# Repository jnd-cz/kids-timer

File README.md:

# Kids timer

Rev 1 PCB design and a MicroPython countdown timer for the RP2354A. The firmware
supports a seven-segment countdown, minute and second LED rings, ambient-light
brightness, audio and songs, battery and sensor readouts, a level, and a touch
pad test.

- [Firmware installation, features and controls](firmware/README.md)
- [Board bring-up and GPIO map](BRINGUP.md)
- [Display power estimate and measurement plan](firmware/POWER.md)
- [Production files for Rev 1](production/)

The firmware is an evolving hardware prototype. See the firmware guide for
features that still need board verification and the 2 MB flash check before
copying files to the device. Run host-side logic checks with
`python -m unittest discover -s tests -v`.

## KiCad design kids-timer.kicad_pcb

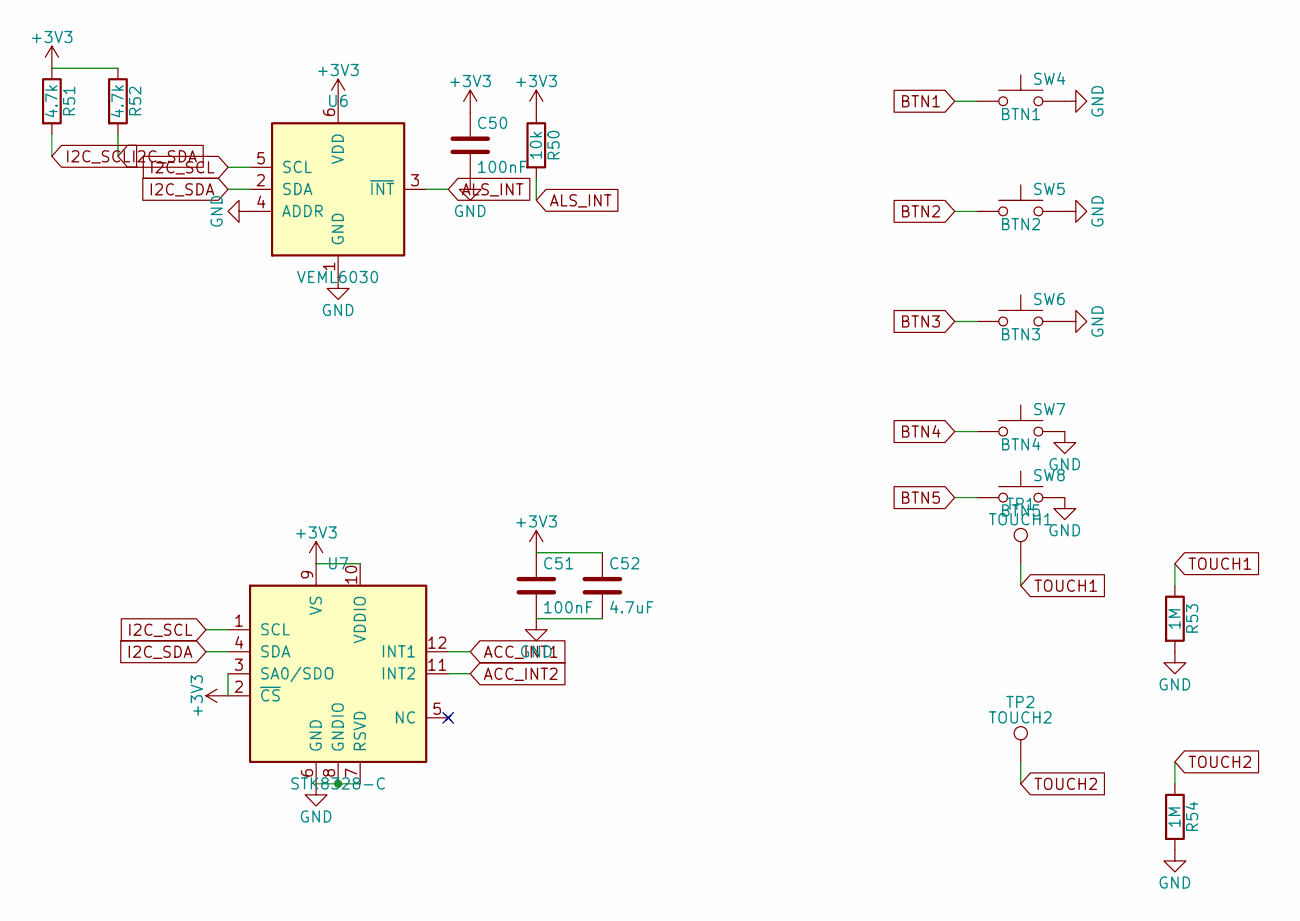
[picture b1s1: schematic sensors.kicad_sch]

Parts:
C50, C51: 100nF; C_0402_1005Metric; LCSC C1525
C52: 4.7uF; C_0402_1005Metric; LCSC C23733
R50: 10k; R_0402_1005Metric; LCSC C25744
R51, R52: 4.7k; R_0402_1005Metric; LCSC C25900
R53, R54: 1M; R_0402_1005Metric; LCSC C26083
SW4: BTN1; SW_SPST_XUNPU_TS-1088_3.9x3mm; MPN TS-1088-AR02016; LCSC C720477
SW5: BTN2; SW_SPST_XUNPU_TS-1088_3.9x3mm; MPN TS-1088-AR02016; LCSC C720477
SW6: BTN3; SW_SPST_XUNPU_TS-1088_3.9x3mm; MPN TS-1088-AR02016; LCSC C720477
SW7: BTN4; SW_SPST_XUNPU_TS-1088_3.9x3mm; MPN TS-1088-AR02016; LCSC C720477
SW8: BTN5; SW_SPST_XUNPU_TS-1088_3.9x3mm; MPN TS-1088-AR02016; LCSC C720477
TP1: TOUCH1; TouchPad_D12mm
TP2: TOUCH2; TouchPad_D12mm
U6: VEML6030; Vishay_VEML6030_2x2mm; MPN VEML6030; LCSC C132182
U7: STK8328-C; LGA-12_2x2mm_P0.5mm; MPN STK8328-C; LCSC C49230199

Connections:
+3V3: C50.1, C51.1, C52.1, R50.1, R51.1, R52.1, U6.6 (VDD), U7.2 (~CS), U7.3 (SA0/SDO), U7.9 (VS), U7.10 (VDDIO); also elsewhere on the board
ACC_INT1: U7.12 (INT1); also elsewhere on the board
ACC_INT2: U7.11 (INT2); also elsewhere on the board
ALS_INT: R50.2, U6.3 (~INT); also elsewhere on the board
BTN1: SW4.1; also elsewhere on the board
BTN2: SW5.1; also elsewhere on the board
BTN3: SW6.1; also elsewhere on the board
BTN4: SW7.1; also elsewhere on the board
BTN5: SW8.1; also elsewhere on the board
I2C_SCL: R51.2, U6.5 (SCL), U7.1 (SCL); also elsewhere on the board
I2C_SDA: R52.2, U6.2 (SDA), U7.4 (SDA); also elsewhere on the board
TOUCH1: R53.1, TP1.1 (1_1); also elsewhere on the board
TOUCH2: R54.1, TP2.1 (1_1); also elsewhere on the board

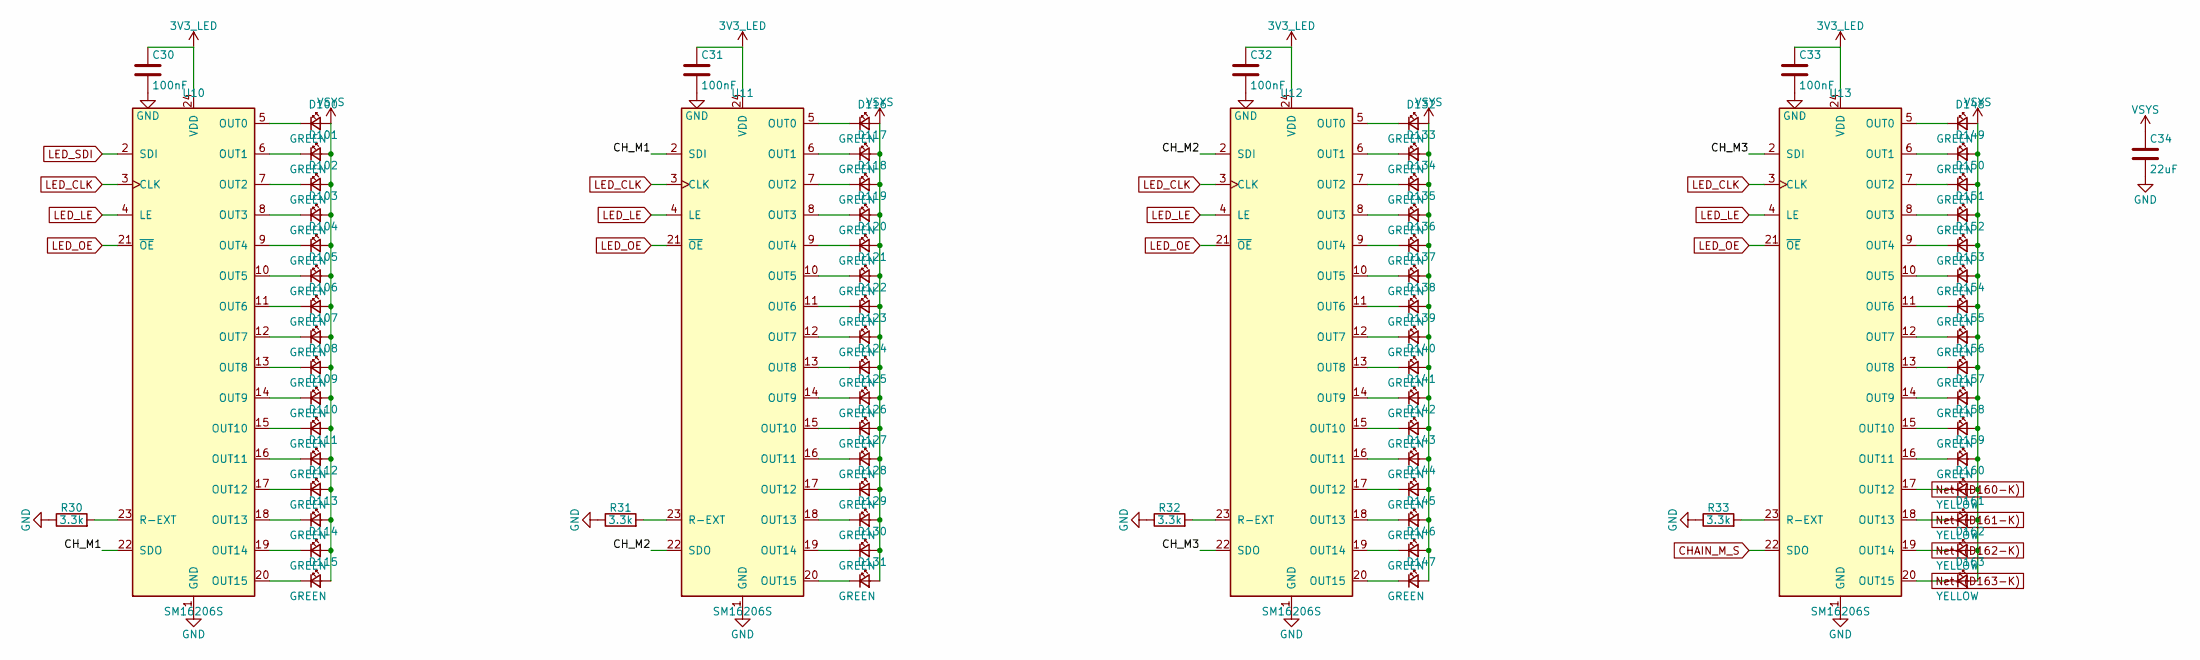
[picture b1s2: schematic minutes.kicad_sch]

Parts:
C30, C31, C32, C33: 100nF; C_0402_1005Metric; LCSC C1525
C34: 22uF; C_0805_2012Metric; LCSC C45783
D100, D101, D102, D103, D104, D105, D106, D107, D108, D109, D110, D111, D112, D113, D114, D115, D116, D117, D118, D119, D120, D121, D122, D123, D124, D125, D126, D127, D128, D129, D130, D131, D132, D133, D134, D135, D136, D137, D138, D139, D140, D141, D142, D143, D144, D145, D146, D147, D148, D149, D150, D151, D152, D153, D154, D155, D156, D157, D158, D159: GREEN; LED_0805_2012Metric_Ring; MPN KT-0805G; LCSC C2297
D160, D161, D162, D163: YELLOW; LED_0805_2012Metric; MPN KT-0805Y; LCSC C2296
R30, R31, R32, R33: 3.3k; R_0402_1005Metric; LCSC C25890
U10, U11, U12, U13: SM16206S; QSOP-24_3.9x8.7mm_P0.635mm; MPN SM16206S; LCSC C121618

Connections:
3V3_LED: C30.1, C31.1, C32.1, C33.1, U10.24 (VDD), U11.24 (VDD), U12.24 (VDD), U13.24 (VDD); also elsewhere on the board
/Minutes ring/CH_M1: U10.22 (SDO), U11.2 (SDI)
/Minutes ring/CH_M2: U11.22 (SDO), U12.2 (SDI)
/Minutes ring/CH_M3: U12.22 (SDO), U13.2 (SDI)
CHAIN_M_S: U13.22 (SDO); also elsewhere on the board
LED_CLK: U10.3 (CLK), U11.3 (CLK), U12.3 (CLK), U13.3 (CLK); also elsewhere on the board
LED_LE: U10.4 (LE), U11.4 (LE), U12.4 (LE), U13.4 (LE); also elsewhere on the board
LED_OE: U10.21 (~OE), U11.21 (~OE), U12.21 (~OE), U13.21 (~OE); also elsewhere on the board
LED_SDI: U10.2 (SDI); also elsewhere on the board
unnamed: D100.1 (K), U10.5 (OUT0)
unnamed: D101.1 (K), U10.6 (OUT1)
unnamed: D102.1 (K), U10.7 (OUT2)
unnamed: D103.1 (K), U10.8 (OUT3)
unnamed: D104.1 (K), U10.9 (OUT4)
unnamed: D105.1 (K), U10.10 (OUT5)
unnamed: D106.1 (K), U10.11 (OUT6)
unnamed: D107.1 (K), U10.12 (OUT7)
unnamed: D108.1 (K), U10.13 (OUT8)
unnamed: D109.1 (K), U10.14 (OUT9)
unnamed: D110.1 (K), U10.15 (OUT10)
unnamed: D111.1 (K), U10.16 (OUT11)
unnamed: D112.1 (K), U10.17 (OUT12)
unnamed: D113.1 (K), U10.18 (OUT13)
unnamed: D114.1 (K), U10.19 (OUT14)
unnamed: D115.1 (K), U10.20 (OUT15)
unnamed: D116.1 (K), U11.5 (OUT0)
unnamed: D117.1 (K), U11.6 (OUT1)
unnamed: D118.1 (K), U11.7 (OUT2)
unnamed: D119.1 (K), U11.8 (OUT3)
unnamed: D120.1 (K), U11.9 (OUT4)
unnamed: D121.1 (K), U11.10 (OUT5)
unnamed: D122.1 (K), U11.11 (OUT6)
unnamed: D123.1 (K), U11.12 (OUT7)
unnamed: D124.1 (K), U11.13 (OUT8)
unnamed: D125.1 (K), U11.14 (OUT9)
unnamed: D126.1 (K), U11.15 (OUT10)
unnamed: D127.1 (K), U11.16 (OUT11)
unnamed: D128.1 (K), U11.17 (OUT12)
unnamed: D129.1 (K), U11.18 (OUT13)
unnamed: D130.1 (K), U11.19 (OUT14)
unnamed: D131.1 (K), U11.20 (OUT15)
unnamed: D132.1 (K), U12.5 (OUT0)
unnamed: D133.1 (K), U12.6 (OUT1)
unnamed: D134.1 (K), U12.7 (OUT2)
unnamed: D135.1 (K), U12.8 (OUT3)
unnamed: D136.1 (K), U12.9 (OUT4)
unnamed: D137.1 (K), U12.10 (OUT5)
unnamed: D138.1 (K), U12.11 (OUT6)
unnamed: D139.1 (K), U12.12 (OUT7)
unnamed: D140.1 (K), U12.13 (OUT8)
unnamed: D141.1 (K), U12.14 (OUT9)
unnamed: D142.1 (K), U12.15 (OUT10)
unnamed: D143.1 (K), U12.16 (OUT11)
unnamed: D144.1 (K), U12.17 (OUT12)
unnamed: D145.1 (K), U12.18 (OUT13)
unnamed: D146.1 (K), U12.19 (OUT14)
unnamed: D147.1 (K), U12.20 (OUT15)
unnamed: D148.1 (K), U13.5 (OUT0)
unnamed: D149.1 (K), U13.6 (OUT1)
unnamed: D150.1 (K), U13.7 (OUT2)
unnamed: D151.1 (K), U13.8 (OUT3)
unnamed: D152.1 (K), U13.9 (OUT4)
unnamed: D153.1 (K), U13.10 (OUT5)
unnamed: D154.1 (K), U13.11 (OUT6)
unnamed: D155.1 (K), U13.12 (OUT7)
unnamed: D156.1 (K), U13.13 (OUT8)
unnamed: D157.1 (K), U13.14 (OUT9)
unnamed: D158.1 (K), U13.15 (OUT10)
unnamed: D159.1 (K), U13.16 (OUT11)
unnamed: D160.1 (K), U13.17 (OUT12)
unnamed: D161.1 (K), U13.18 (OUT13)
unnamed: D162.1 (K), U13.19 (OUT14)
unnamed: D163.1 (K), U13.20 (OUT15)
unnamed: R30.2, U10.23 (R-EXT)
unnamed: R31.2, U11.23 (R-EXT)
unnamed: R32.2, U12.23 (R-EXT)
unnamed: R33.2, U13.23 (R-EXT)
VSYS: C34.1, D100.2 (A), D101.2 (A), D102.2 (A), D103.2 (A), D104.2 (A), D105.2 (A), D106.2 (A), D107.2 (A), D108.2 (A), D109.2 (A), D110.2 (A), D111.2 (A), D112.2 (A), D113.2 (A), D114.2 (A), D115.2 (A), D116.2 (A), D117.2 (A), D118.2 (A), D119.2 (A), D120.2 (A), D121.2 (A), D122.2 (A), D123.2 (A), D124.2 (A), D125.2 (A), D126.2 (A), D127.2 (A), D128.2 (A), D129.2 (A), D130.2 (A), D131.2 (A), D132.2 (A), D133.2 (A), D134.2 (A), D135.2 (A), D136.2 (A), D137.2 (A), D138.2 (A), D139.2 (A), D140.2 (A), D141.2 (A), D142.2 (A), D143.2 (A), D144.2 (A), D145.2 (A), D146.2 (A), D147.2 (A), D148.2 (A), D149.2 (A), D150.2 (A), D151.2 (A), D152.2 (A), D153.2 (A), D154.2 (A), D155.2 (A), D156.2 (A), D157.2 (A), D158.2 (A), D159.2 (A), D160.2 (A), D161.2 (A), D162.2 (A), D163.2 (A); also elsewhere on the board

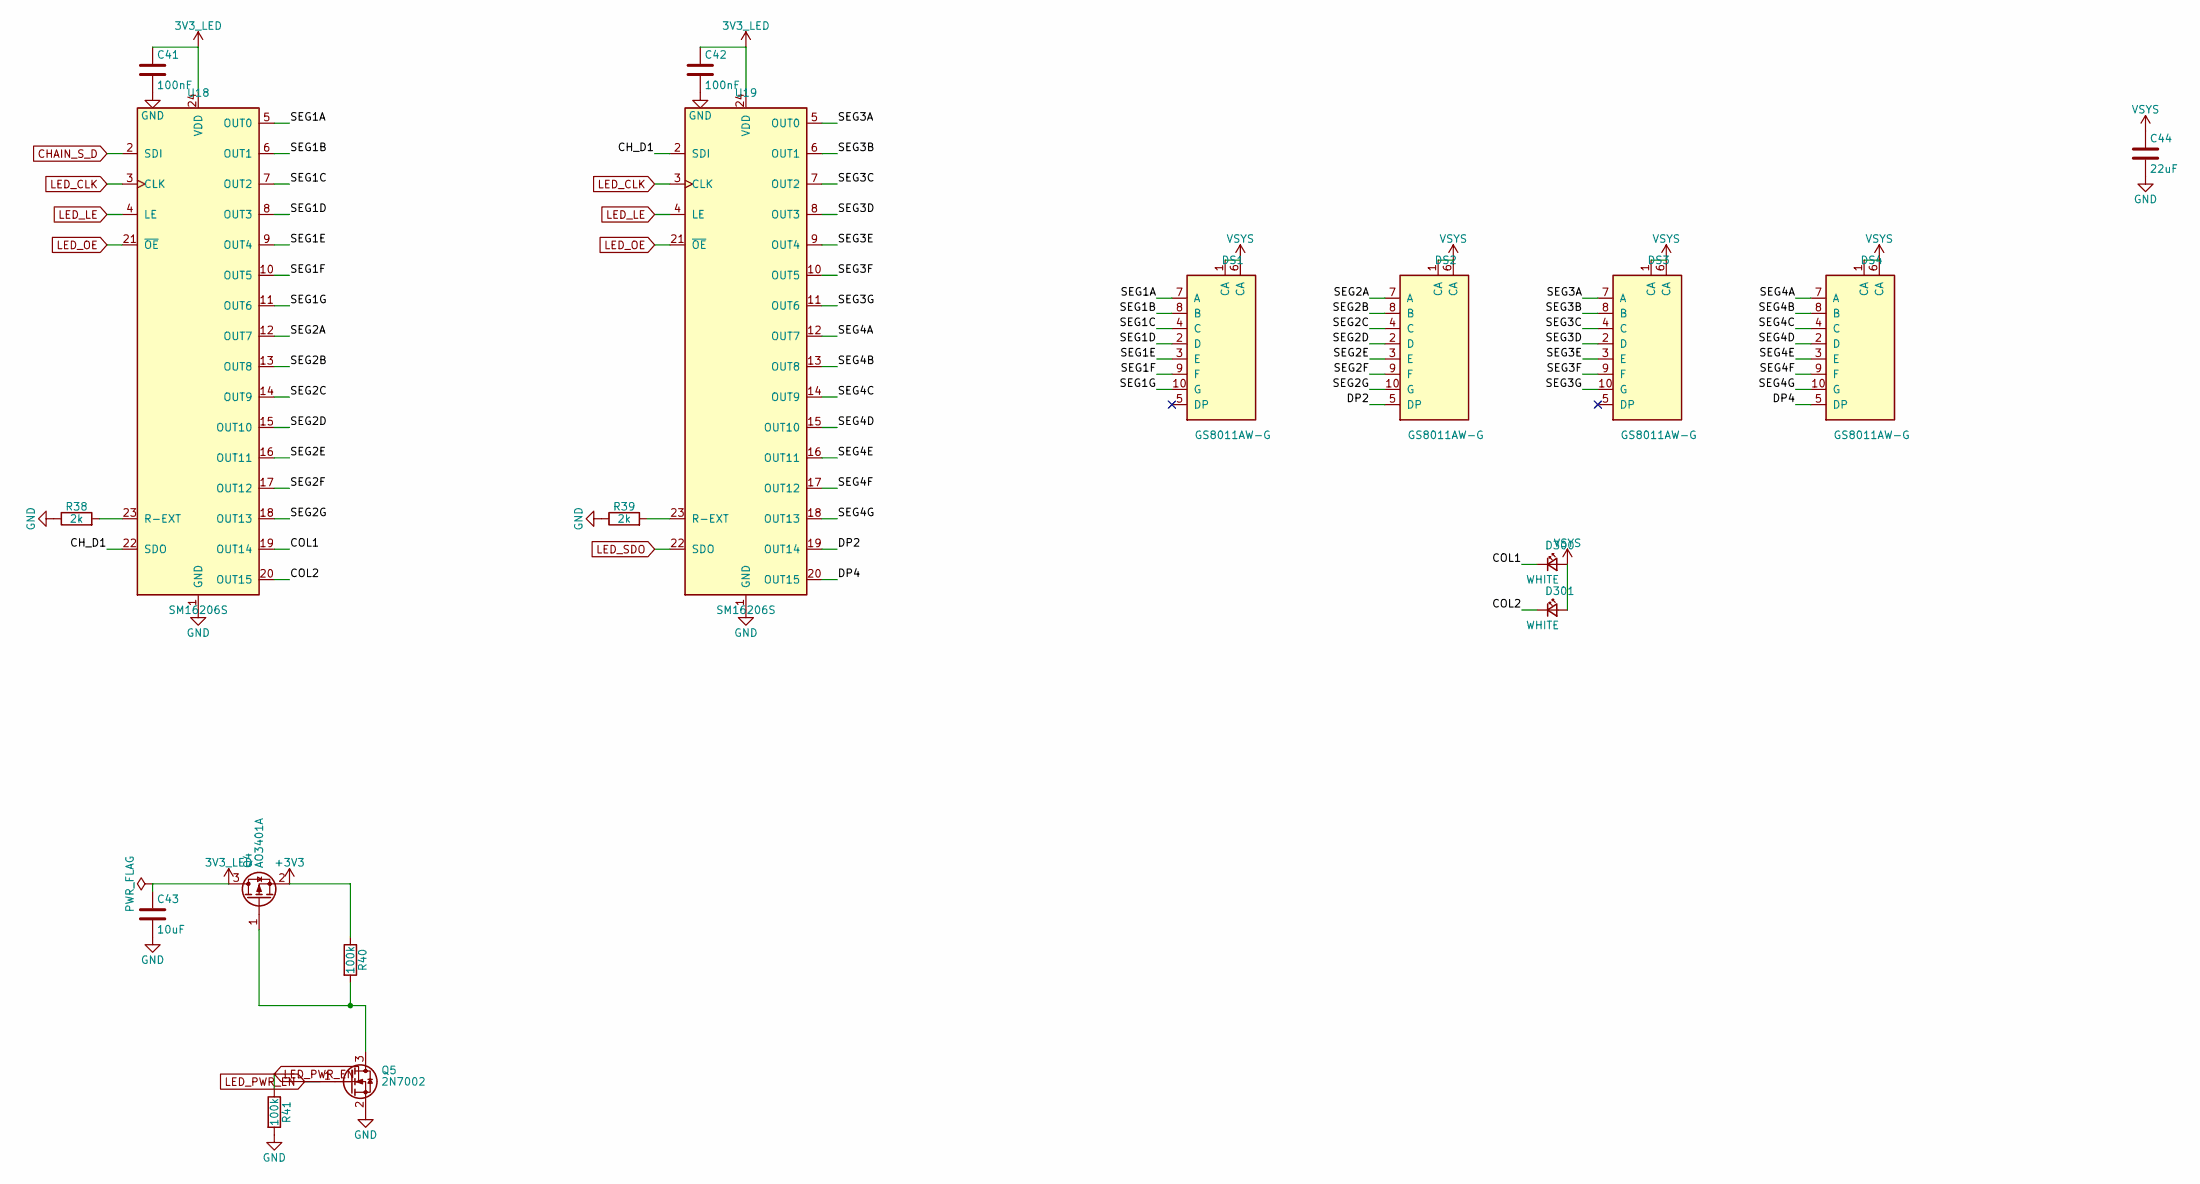
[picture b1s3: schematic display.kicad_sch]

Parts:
C41, C42: 100nF; C_0402_1005Metric; LCSC C1525
C43: 10uF; C_0805_2012Metric; LCSC C15850
C44: 22uF; C_0805_2012Metric; LCSC C45783
D300, D301: WHITE; LED_0805_2012Metric; LCSC C34499
DS1, DS2, DS3, DS4: GS8011AW-G; GS8011_SMD_16.8x28mm; LCSC C22462707
Q4: AO3401A; SOT-23; LCSC C15127
Q5: 2N7002; SOT-23; LCSC C8545
R38, R39: 2k; R_0402_1005Metric; LCSC C4109
R40, R41: 100k; R_0402_1005Metric; LCSC C25741
U18, U19: SM16206S; QSOP-24_3.9x8.7mm_P0.635mm; LCSC C121618

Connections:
3V3_LED: C41.1, C42.1, C43.1, Q4.3 (D), U18.24 (VDD), U19.24 (VDD); also elsewhere on the board
+3V3: Q4.2 (S), R40.1; also elsewhere on the board
/Display/CH_D1: U18.22 (SDO), U19.2 (SDI)
/Display/COL1: D300.1 (K), U18.19 (OUT14)
/Display/COL2: D301.1 (K), U18.20 (OUT15)
/Display/DP2: DS2.5 (DP), U19.19 (OUT14)
/Display/DP4: DS4.5 (DP), U19.20 (OUT15)
/Display/SEG1A: DS1.7 (A), U18.5 (OUT0)
/Display/SEG1B: DS1.8 (B), U18.6 (OUT1)
/Display/SEG1C: DS1.4 (C), U18.7 (OUT2)
/Display/SEG1D: DS1.2 (D), U18.8 (OUT3)
/Display/SEG1E: DS1.3 (E), U18.9 (OUT4)
/Display/SEG1F: DS1.9 (F), U18.10 (OUT5)
/Display/SEG1G: DS1.10 (G), U18.11 (OUT6)
/Display/SEG2A: DS2.7 (A), U18.12 (OUT7)
/Display/SEG2B: DS2.8 (B), U18.13 (OUT8)
/Display/SEG2C: DS2.4 (C), U18.14 (OUT9)
/Display/SEG2D: DS2.2 (D), U18.15 (OUT10)
/Display/SEG2E: DS2.3 (E), U18.16 (OUT11)
/Display/SEG2F: DS2.9 (F), U18.17 (OUT12)
/Display/SEG2G: DS2.10 (G), U18.18 (OUT13)
/Display/SEG3A: DS3.7 (A), U19.5 (OUT0)
/Display/SEG3B: DS3.8 (B), U19.6 (OUT1)
/Display/SEG3C: DS3.4 (C), U19.7 (OUT2)
/Display/SEG3D: DS3.2 (D), U19.8 (OUT3)
/Display/SEG3E: DS3.3 (E), U19.9 (OUT4)
/Display/SEG3F: DS3.9 (F), U19.10 (OUT5)
/Display/SEG3G: DS3.10 (G), U19.11 (OUT6)
/Display/SEG4A: DS4.7 (A), U19.12 (OUT7)
/Display/SEG4B: DS4.8 (B), U19.13 (OUT8)
/Display/SEG4C: DS4.4 (C), U19.14 (OUT9)
/Display/SEG4D: DS4.2 (D), U19.15 (OUT10)
/Display/SEG4E: DS4.3 (E), U19.16 (OUT11)
/Display/SEG4F: DS4.9 (F), U19.17 (OUT12)
/Display/SEG4G: DS4.10 (G), U19.18 (OUT13)
CHAIN_S_D: U18.2 (SDI); also elsewhere on the board
LED_CLK: U18.3 (CLK), U19.3 (CLK); also elsewhere on the board
LED_LE: U18.4 (LE), U19.4 (LE); also elsewhere on the board
LED_OE: U18.21 (~OE), U19.21 (~OE); also elsewhere on the board
LED_PWR_EN: Q5.1 (G), R41.1; also elsewhere on the board
LED_SDO: U19.22 (SDO); also elsewhere on the board
unnamed: Q4.1 (G), Q5.3 (D), R40.2
unnamed: R38.2, U18.23 (R-EXT)
unnamed: R39.2, U19.23 (R-EXT)
VSYS: C44.1, D300.2 (A), D301.2 (A), DS1.1 (CA), DS1.6 (CA), DS2.1 (CA), DS2.6 (CA), DS3.1 (CA), DS3.6 (CA), DS4.1 (CA), DS4.6 (CA); also elsewhere on the board

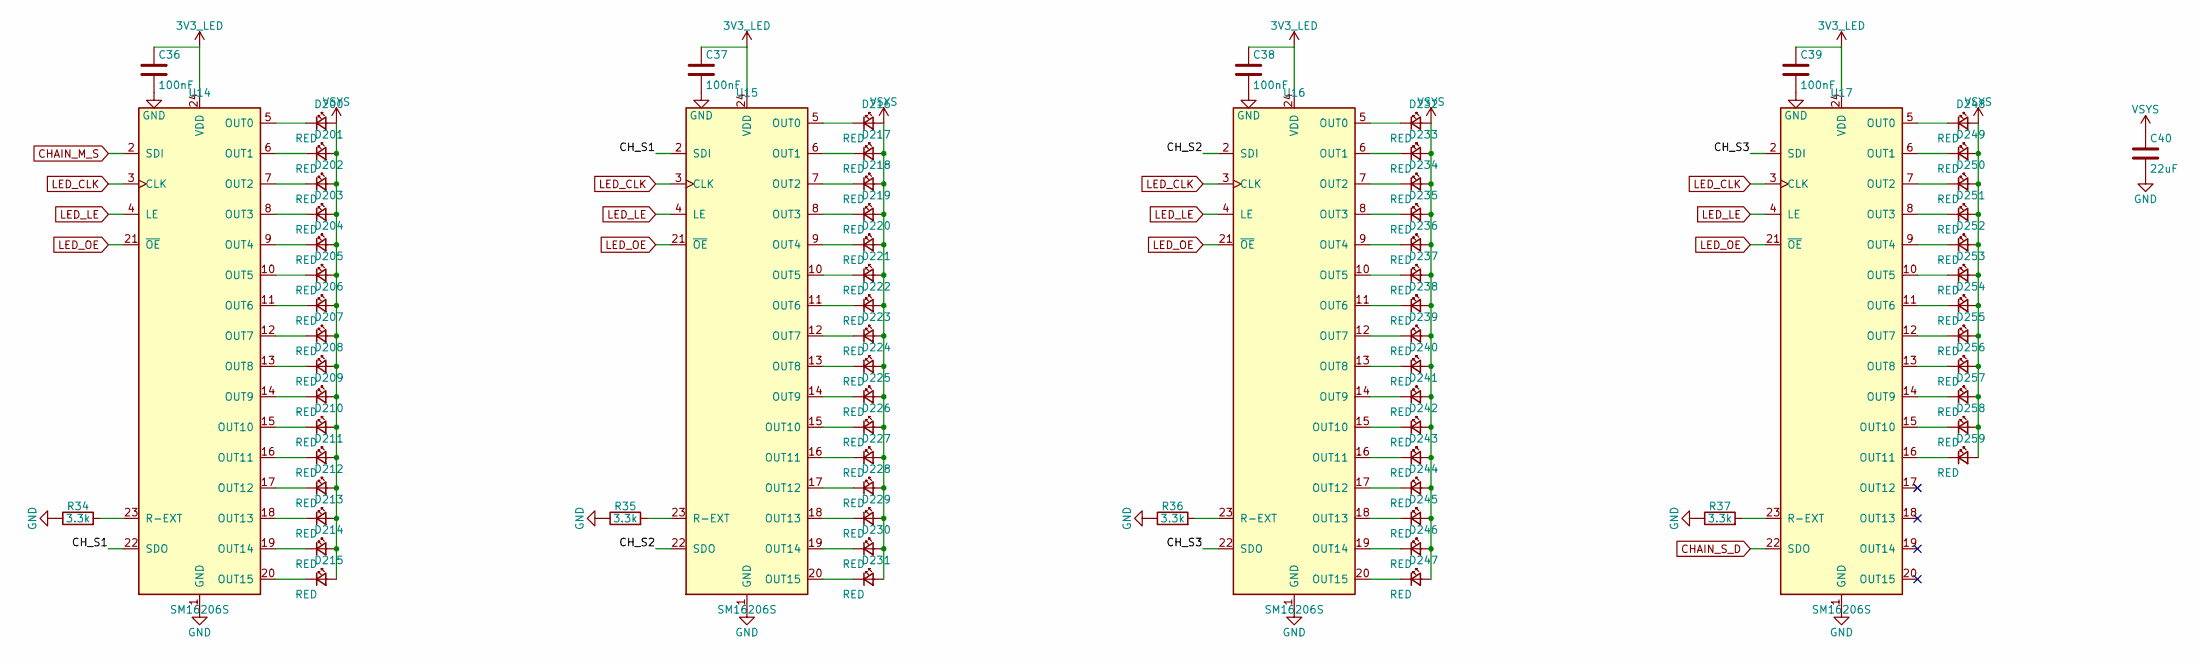
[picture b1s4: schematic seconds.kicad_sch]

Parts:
C36, C37, C38, C39: 100nF; C_0402_1005Metric; LCSC C1525
C40: 22uF; C_0805_2012Metric; LCSC C45783
D200, D201, D202, D203, D204, D205, D206, D207, D208, D209, D210, D211, D212, D213, D214, D215, D216, D217, D218, D219, D220, D221, D222, D223, D224, D225, D226, D227, D228, D229, D230, D231, D232, D233, D234, D235, D236, D237, D238, D239, D240, D241, D242, D243, D244, D245, D246, D247, D248, D249, D250, D251, D252, D253, D254, D255, D256, D257, D258, D259: RED; LED_0805_2012Metric_Ring; LCSC C84256
R34, R35, R36, R37: 3.3k; R_0402_1005Metric; LCSC C25890
U14, U15, U16, U17: SM16206S; QSOP-24_3.9x8.7mm_P0.635mm; LCSC C121618

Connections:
3V3_LED: C36.1, C37.1, C38.1, C39.1, U14.24 (VDD), U15.24 (VDD), U16.24 (VDD), U17.24 (VDD); also elsewhere on the board
/Seconds ring/CH_S1: U14.22 (SDO), U15.2 (SDI)
/Seconds ring/CH_S2: U15.22 (SDO), U16.2 (SDI)
/Seconds ring/CH_S3: U16.22 (SDO), U17.2 (SDI)
CHAIN_M_S: U14.2 (SDI); also elsewhere on the board
CHAIN_S_D: U17.22 (SDO); also elsewhere on the board
LED_CLK: U14.3 (CLK), U15.3 (CLK), U16.3 (CLK), U17.3 (CLK); also elsewhere on the board
LED_LE: U14.4 (LE), U15.4 (LE), U16.4 (LE), U17.4 (LE); also elsewhere on the board
LED_OE: U14.21 (~OE), U15.21 (~OE), U16.21 (~OE), U17.21 (~OE); also elsewhere on the board
unnamed: D200.1 (K), U14.5 (OUT0)
unnamed: D201.1 (K), U14.6 (OUT1)
unnamed: D202.1 (K), U14.7 (OUT2)
unnamed: D203.1 (K), U14.8 (OUT3)
unnamed: D204.1 (K), U14.9 (OUT4)
unnamed: D205.1 (K), U14.10 (OUT5)
unnamed: D206.1 (K), U14.11 (OUT6)
unnamed: D207.1 (K), U14.12 (OUT7)
unnamed: D208.1 (K), U14.13 (OUT8)
unnamed: D209.1 (K), U14.14 (OUT9)
unnamed: D210.1 (K), U14.15 (OUT10)
unnamed: D211.1 (K), U14.16 (OUT11)
unnamed: D212.1 (K), U14.17 (OUT12)
unnamed: D213.1 (K), U14.18 (OUT13)
unnamed: D214.1 (K), U14.19 (OUT14)
unnamed: D215.1 (K), U14.20 (OUT15)
unnamed: D216.1 (K), U15.5 (OUT0)
unnamed: D217.1 (K), U15.6 (OUT1)
unnamed: D218.1 (K), U15.7 (OUT2)
unnamed: D219.1 (K), U15.8 (OUT3)
unnamed: D220.1 (K), U15.9 (OUT4)
unnamed: D221.1 (K), U15.10 (OUT5)
unnamed: D222.1 (K), U15.11 (OUT6)
unnamed: D223.1 (K), U15.12 (OUT7)
unnamed: D224.1 (K), U15.13 (OUT8)
unnamed: D225.1 (K), U15.14 (OUT9)
unnamed: D226.1 (K), U15.15 (OUT10)
unnamed: D227.1 (K), U15.16 (OUT11)
unnamed: D228.1 (K), U15.17 (OUT12)
unnamed: D229.1 (K), U15.18 (OUT13)
unnamed: D230.1 (K), U15.19 (OUT14)
unnamed: D231.1 (K), U15.20 (OUT15)
unnamed: D232.1 (K), U16.5 (OUT0)
unnamed: D233.1 (K), U16.6 (OUT1)
unnamed: D234.1 (K), U16.7 (OUT2)
unnamed: D235.1 (K), U16.8 (OUT3)
unnamed: D236.1 (K), U16.9 (OUT4)
unnamed: D237.1 (K), U16.10 (OUT5)
unnamed: D238.1 (K), U16.11 (OUT6)
unnamed: D239.1 (K), U16.12 (OUT7)
unnamed: D240.1 (K), U16.13 (OUT8)
unnamed: D241.1 (K), U16.14 (OUT9)
unnamed: D242.1 (K), U16.15 (OUT10)
unnamed: D243.1 (K), U16.16 (OUT11)
unnamed: D244.1 (K), U16.17 (OUT12)
unnamed: D245.1 (K), U16.18 (OUT13)
unnamed: D246.1 (K), U16.19 (OUT14)
unnamed: D247.1 (K), U16.20 (OUT15)
unnamed: D248.1 (K), U17.5 (OUT0)
unnamed: D249.1 (K), U17.6 (OUT1)
unnamed: D250.1 (K), U17.7 (OUT2)
unnamed: D251.1 (K), U17.8 (OUT3)
unnamed: D252.1 (K), U17.9 (OUT4)
unnamed: D253.1 (K), U17.10 (OUT5)
unnamed: D254.1 (K), U17.11 (OUT6)
unnamed: D255.1 (K), U17.12 (OUT7)
unnamed: D256.1 (K), U17.13 (OUT8)
unnamed: D257.1 (K), U17.14 (OUT9)
unnamed: D258.1 (K), U17.15 (OUT10)
unnamed: D259.1 (K), U17.16 (OUT11)
unnamed: R34.2, U14.23 (R-EXT)
unnamed: R35.2, U15.23 (R-EXT)
unnamed: R36.2, U16.23 (R-EXT)
unnamed: R37.2, U17.23 (R-EXT)
VSYS: C40.1, D200.2 (A), D201.2 (A), D202.2 (A), D203.2 (A), D204.2 (A), D205.2 (A), D206.2 (A), D207.2 (A), D208.2 (A), D209.2 (A), D210.2 (A), D211.2 (A), D212.2 (A), D213.2 (A), D214.2 (A), D215.2 (A), D216.2 (A), D217.2 (A), D218.2 (A), D219.2 (A), D220.2 (A), D221.2 (A), D222.2 (A), D223.2 (A), D224.2 (A), D225.2 (A), D226.2 (A), D227.2 (A), D228.2 (A), D229.2 (A), D230.2 (A), D231.2 (A), D232.2 (A), D233.2 (A), D234.2 (A), D235.2 (A), D236.2 (A), D237.2 (A), D238.2 (A), D239.2 (A), D240.2 (A), D241.2 (A), D242.2 (A), D243.2 (A), D244.2 (A), D245.2 (A), D246.2 (A), D247.2 (A), D248.2 (A), D249.2 (A), D250.2 (A), D251.2 (A), D252.2 (A), D253.2 (A), D254.2 (A), D255.2 (A), D256.2 (A), D257.2 (A), D258.2 (A), D259.2 (A); also elsewhere on the board

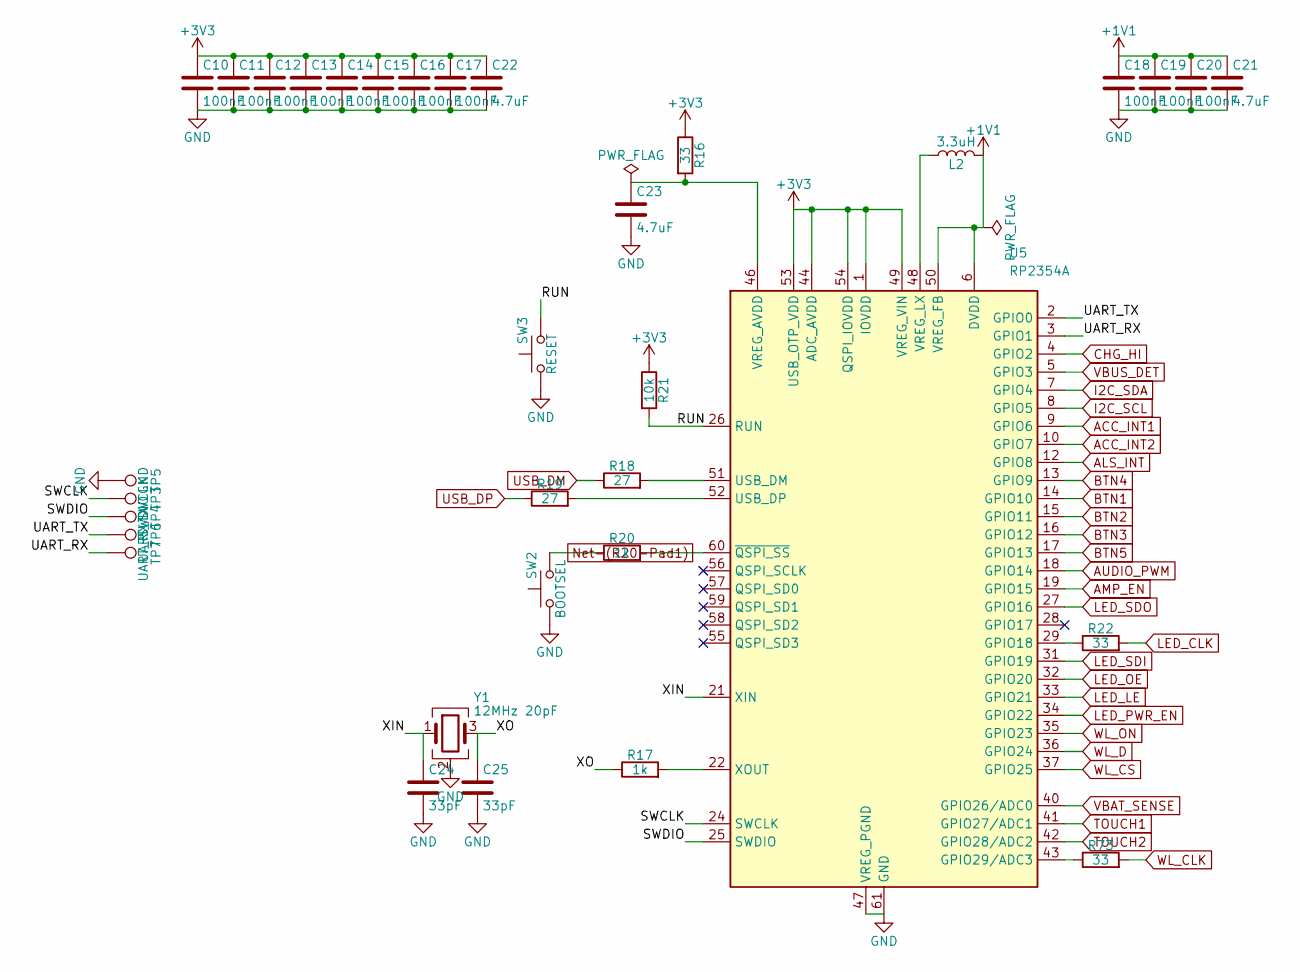
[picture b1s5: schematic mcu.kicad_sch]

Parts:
C10, C11, C12, C13, C14, C15, C16, C17, C18, C19, C20: 100nF; C_0402_1005Metric; LCSC C1525
C21, C22, C23: 4.7uF; C_0402_1005Metric; LCSC C23733
C24, C25: 33pF; C_0402_1005Metric; MPN 0402CG330J500NT; LCSC C1562
L2: 3.3uH; L_Changjiang_FTC201612S; MPN YSMC201612H-3R3MB; LCSC C41405891
R16, R22, R73: 33; R_0402_1005Metric; LCSC C25105
R17, R20: 1k; R_0402_1005Metric; LCSC C11702
R18, R19: 27; R_0603_1608Metric; LCSC C25190
R21: 10k; R_0402_1005Metric; LCSC C25744
SW2: BOOTSEL; SW_SPST_XUNPU_TS-1088_3.9x3mm; MPN TS-1088-AR02016; LCSC C720477
SW3: RESET; SW_SPST_XUNPU_TS-1088_3.9x3mm; MPN TS-1088-AR02016; LCSC C720477
TP3: SWCLK; TestPoint_Pad_D1.5mm
TP4: SWDIO; TestPoint_Pad_D1.5mm
TP5: GND; TestPoint_Pad_D1.5mm
TP6: UART_TX; TestPoint_Pad_D1.5mm
TP7: UART_RX; TestPoint_Pad_D1.5mm
U5: RP2354A; QFN-60-1EP_7x7mm_P0.4mm_EP3.4x3.4mm; MPN RP2354A; LCSC C41378174
Y1: 12MHz 20pF; Crystal_SMD_3225-4Pin_3.2x2.5mm; MPN X322512MSB4SI; LCSC C9002

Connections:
+3V3: C10.1, C11.1, C12.1, C13.1, C14.1, C15.1, C16.1, C17.1, C22.1, R16.1, R21.1, U5.1 (IOVDD), U5.11 (IOVDD), U5.20 (IOVDD), U5.30 (IOVDD), U5.38 (IOVDD), U5.44 (ADC_AVDD), U5.45 (IOVDD), U5.49 (VREG_VIN), U5.53 (USB_OTP_VDD), U5.54 (QSPI_IOVDD); also elsewhere on the board
/MCU/RUN: R21.2, SW3.2, U5.26 (RUN)
/MCU/SWCLK: TP3.1 (1_1), U5.24 (SWCLK)
/MCU/SWDIO: TP4.1 (1_1), U5.25 (SWDIO)
/MCU/UART_RX: TP7.1 (1_1), U5.3 (GPIO1)
/MCU/UART_TX: TP6.1 (1_1), U5.2 (GPIO0)
/MCU/XIN: C24.1, U5.21 (XIN), Y1.1
/MCU/XO: C25.1, R17.1, Y1.3
ACC_INT1: U5.9 (GPIO6); also elsewhere on the board
ACC_INT2: U5.10 (GPIO7); also elsewhere on the board
ALS_INT: U5.12 (GPIO8); also elsewhere on the board
AMP_EN: U5.19 (GPIO15); also elsewhere on the board
AUDIO_PWM: U5.18 (GPIO14); also elsewhere on the board
BTN1: U5.14 (GPIO10); also elsewhere on the board
BTN2: U5.15 (GPIO11); also elsewhere on the board
BTN3: U5.16 (GPIO12); also elsewhere on the board
BTN4: U5.13 (GPIO9); also elsewhere on the board
BTN5: U5.17 (GPIO13); also elsewhere on the board
CHG_HI: U5.4 (GPIO2); also elsewhere on the board
I2C_SCL: U5.8 (GPIO5); also elsewhere on the board
I2C_SDA: U5.7 (GPIO4); also elsewhere on the board
LED_CLK: R22.2; also elsewhere on the board
LED_LE: U5.33 (GPIO21); also elsewhere on the board
LED_OE: U5.32 (GPIO20); also elsewhere on the board
LED_PWR_EN: U5.34 (GPIO22); also elsewhere on the board
LED_SDI: U5.31 (GPIO19); also elsewhere on the board
LED_SDO: U5.27 (GPIO16); also elsewhere on the board
unnamed: R20.1, SW2.2
unnamed: R22.1, U5.29 (GPIO18)
unnamed: R73.1, U5.43 (GPIO29/ADC3)
unnamed: R18.2, U5.51 (USB_DM)
unnamed: R19.2, U5.52 (USB_DP)
unnamed: L2.1, U5.48 (VREG_LX)
unnamed: R17.2, U5.22 (XOUT)
unnamed: R20.2, U5.60 (~QSPI_SS)
TOUCH1: U5.41 (GPIO27/ADC1); also elsewhere on the board
TOUCH2: U5.42 (GPIO28/ADC2); also elsewhere on the board
USB_DM: R18.1; also elsewhere on the board
USB_DP: R19.1; also elsewhere on the board
VBAT_SENSE: U5.40 (GPIO26/ADC0); also elsewhere on the board
VBUS_DET: U5.5 (GPIO3); also elsewhere on the board
WL_CLK: R73.2; also elsewhere on the board
WL_CS: U5.37 (GPIO25); also elsewhere on the board
WL_D: U5.36 (GPIO24); also elsewhere on the board
WL_ON: U5.35 (GPIO23); also elsewhere on the board

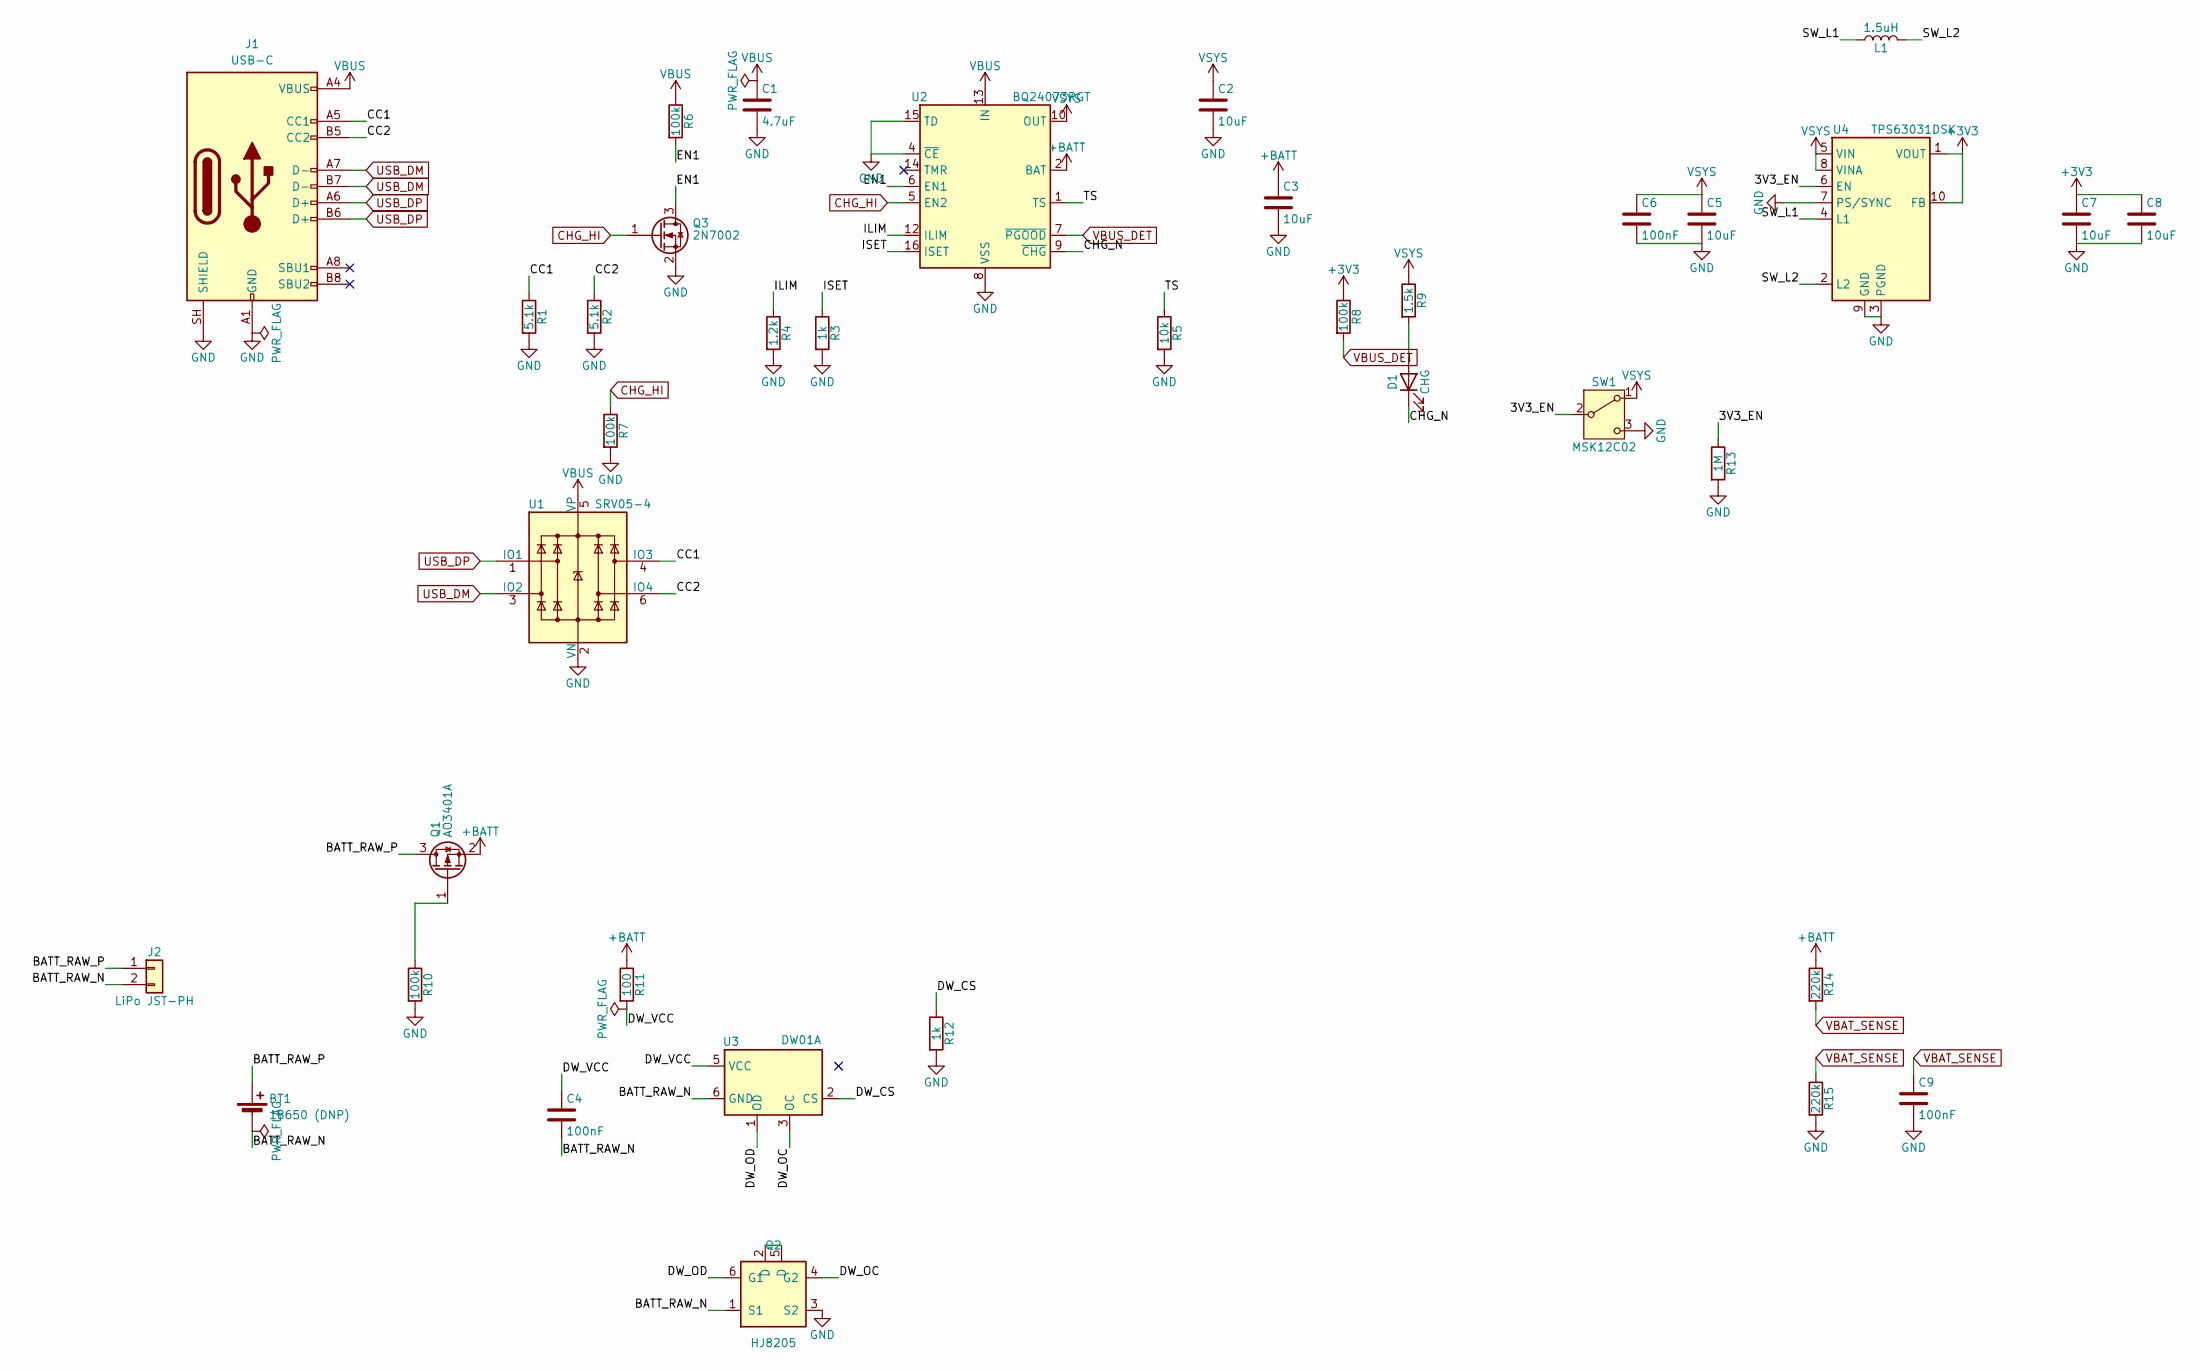
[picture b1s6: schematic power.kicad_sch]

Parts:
BT1: 18650 (DNP)
C1: 4.7uF; C_0805_2012Metric; LCSC C1779
C2, C3, C5, C7, C8: 10uF; C_0805_2012Metric; LCSC C15850
C4, C6, C9: 100nF; C_0603_1608Metric; LCSC C14663
D1: CHG; LED_0603_1608Metric; MPN KT-0603R; LCSC C2286
J1: USB-C; USB_C_Receptacle_HRO_TYPE-C-31-M-12; MPN TYPE-C-31-M-12; LCSC C165948
J2: LiPo JST-PH; JST_PH_S2B-PH-SM4-TB_1x02-1MP_P2.00mm_Horizontal; MPN S2B-PH-SM4-TB(LF)(SN); LCSC C295747
L1: 1.5uH; L_1008_2520Metric; MPN WPN252012H1R5MT; LCSC C98349
Q1: AO3401A; SOT-23; MPN AO3401A; LCSC C15127
Q2: HJ8205; SOT-23-6; MPN HJ8205; LCSC C20069150
Q3: 2N7002; SOT-23; LCSC C8545
R1, R2: 5.1k; R_0603_1608Metric; LCSC C23186
R3, R12: 1k; R_0603_1608Metric; LCSC C21190
R4: 1.2k; R_0603_1608Metric; LCSC C22765
R5: 10k; R_0603_1608Metric; LCSC C25804
R6, R7, R8, R10: 100k; R_0603_1608Metric; LCSC C25803
R9: 1.5k; R_0603_1608Metric; LCSC C22843
R11: 100; R_0603_1608Metric; LCSC C22775
R13: 1M; R_0603_1608Metric; LCSC C22935
R14, R15: 220k; R_0603_1608Metric; LCSC C22961
SW1: MSK12C02; SW_SPDT_MSK12C02_EdgeNotch; MPN MSK12C02G15-B; LCSC C22435661
U1: SRV05-4; SOT-23-6; MPN SRV05-4-P-T7; LCSC C85364
U2: BQ24073RGT; VQFN-16-1EP_3x3mm_P0.5mm_EP1.6x1.6mm; MPN BQ24073RGTR; LCSC C15220
U3: DW01A; SOT-23-6; MPN DW01A; LCSC C42380662
U4: TPS63031DSK; WSON-10-1EP_2.5x2.5mm_P0.5mm_EP1.2x2mm; MPN TPS63031DSKR; LCSC C15516

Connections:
+3V3: C7.1, C8.1, R8.1, U4.1 (VOUT), U4.10 (FB); also elsewhere on the board
+BATT: C3.1, Q1.2 (S), R11.1, R14.1, U2.2 (BAT), U2.3 (BAT)
/Power/3V3_EN: R13.1, SW1.2 (B), U4.6 (EN)
/Power/BATT_RAW_P: BT1.1 (+), J2.1, Q1.3 (D)
/Power/CC1: J1.A5 (CC1), R1.1, U1.4 (IO3)
/Power/CC2: J1.B5 (CC2), R2.1, U1.6 (IO4)
/Power/CHG_N: D1.1 (K), U2.9 (~CHG)
/Power/DW_CS: R12.1, U3.2 (CS)
/Power/DW_OC: Q2.4 (G2), U3.3 (OC)
/Power/DW_OD: Q2.6 (G1), U3.1 (OD)
/Power/EN1: Q3.3 (D), R6.2, U2.6 (EN1)
/Power/ILIM: R4.1, U2.12 (ILIM)
/Power/ISET: R3.1, U2.16 (ISET)
/Power/SW_L1: L1.1, U4.4 (L1)
/Power/SW_L2: L1.2, U4.2 (L2)
/Power/TS: R5.1, U2.1 (TS)
CHG_HI: Q3.1 (G), R7.1, U2.5 (EN2); also elsewhere on the board
unnamed: D1.2 (A), R9.2
unnamed: Q1.1 (G), R10.1
unnamed: Q2.2 (D), Q2.5 (D)
USB_DM: J1.A7 (D-), J1.B7 (D-), U1.3 (IO2); also elsewhere on the board
USB_DP: J1.A6 (D+), J1.B6 (D+), U1.1 (IO1); also elsewhere on the board
VBAT_SENSE: C9.1, R14.2, R15.1; also elsewhere on the board
VBUS_DET: R8.2, U2.7 (~PGOOD); also elsewhere on the board
VSYS: C2.1, C5.1, C6.1, R9.1, SW1.1 (A), U2.10 (OUT), U2.11 (OUT), U4.5 (VIN), U4.8 (VINA); also elsewhere on the board
